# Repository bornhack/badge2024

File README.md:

# BornHack badge 2024

## Firmware

[Initial firmware](https://github.com/badgeteam/bornhack2024-firmware) ([Flasher tool](https://github.com/badgeteam/bornhack2024-flasher))

[Pwnies ESP32-C3 Firmware Examples](https://github.com/Pwnies/bornhack-badge-esp32-c3-rust)

[Orange Murker workshop POV firmware](https://github.com/Orange-Murker/bh25-rs)

[3D Printed Case](https://github.com/bornhack/badge2024/tree/case)

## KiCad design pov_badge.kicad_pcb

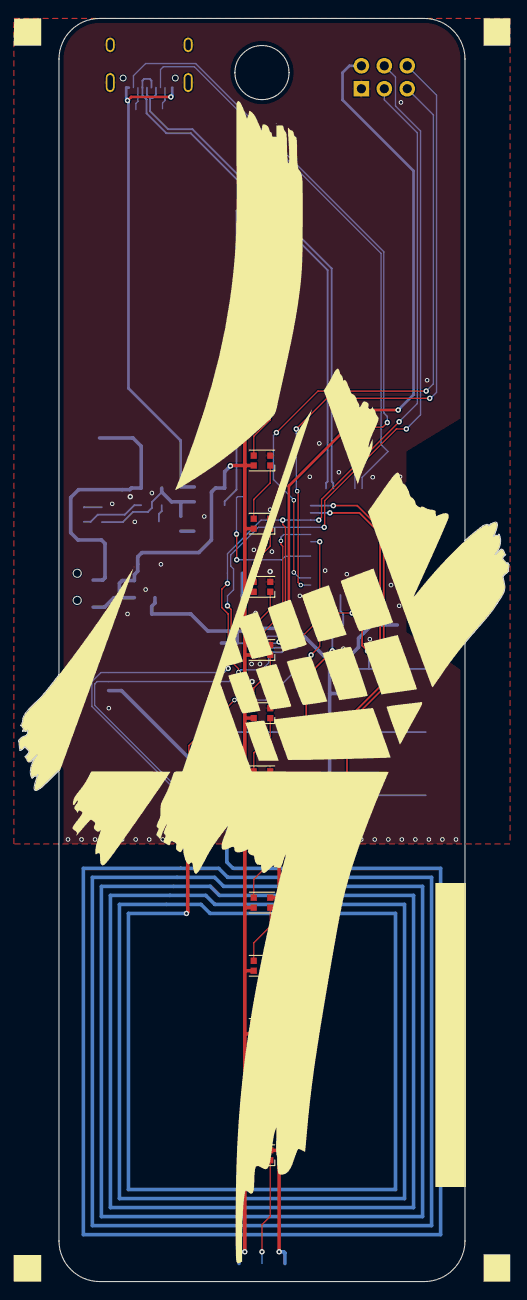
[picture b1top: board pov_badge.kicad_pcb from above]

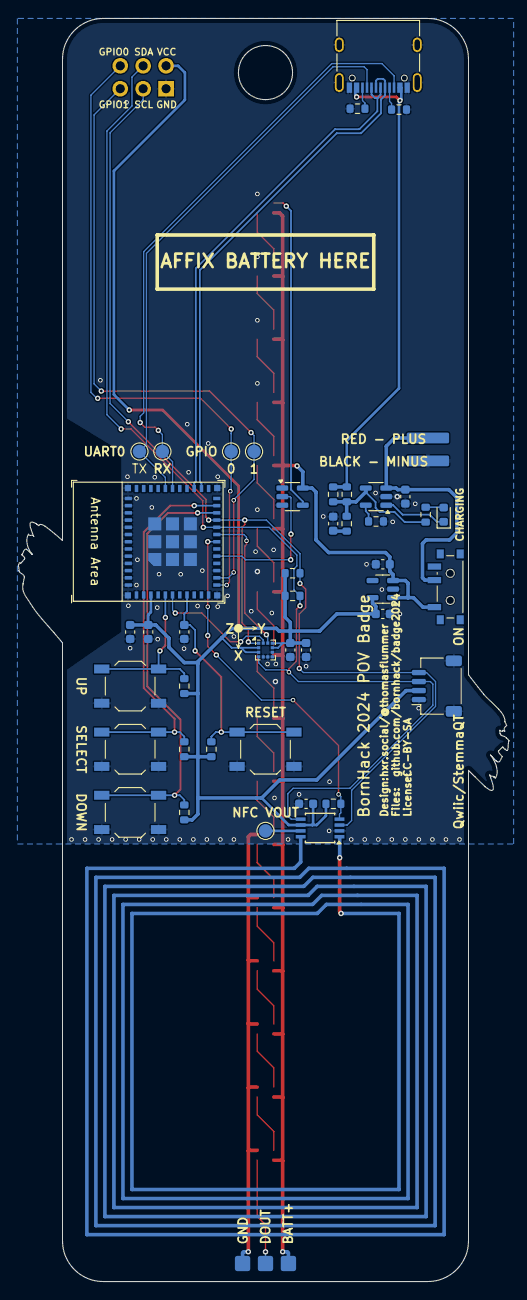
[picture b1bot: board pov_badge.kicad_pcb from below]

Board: 2 copper layers, 54.4 x 140.0 mm, 62 parts (45 on the bottom side), 47 nets.

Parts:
C1, C8, C10: 100nF; C_0603_1608Metric
C2: 4.7uF; C_0603_1608Metric
C3, C4, C7: 1uF; C_0603_1608Metric
C5: 100nf; C_0603_1608Metric
C6, C9: 10uF; C_0603_1608Metric
D1, D2, D3, D4, D5, D6, D7, D8, D9, D10, D11, D12, D13, D14, D15, D16: WS2812B-2020; LED_WS2812B-2020_PLCC4_2.0x2.0mm
D17: CHRG; LED_0603_1608Metric
J1: LED_OUT; PinHeader_1x03_P2.54mm_Horizontal
J2: LiPo 1S; PinHeader_1x02_P2.54mm_Vertical
J3: USB_C_Receptacle_USB2.0_16P; USB_C_Receptacle_XKB_U262-16XN-4BVC11
J4: Qwiic; JST_SH_SM04B-SRSS-TB_1x04-1MP_P1.00mm_Horizontal
R1, R11, R12, R13, R14: 10K; R_0603_1608Metric
R2, R4, R5: 1; R_0603_1608Metric
R3: 1k; R_0603_1608Metric
R6: 2k; R_0603_1608Metric
R7, R8: 10k; R_0603_1608Metric
R9, R10: 5.1K; R_0603_1608Metric
SW1: UP; SW_SPST_TL3342
SW2: DOWN; SW_SPST_TL3342
SW3: POWER; SW_SPDT_PCM12
SW4: RESET; SW_SPST_TL3342
SW5: SELECT; SW_SPST_TL3342
TP1: NFC_VOUT; TestPoint_Pad_D1.5mm
TP2: GPIO1; TestPoint_Pad_D1.5mm
TP3: GPIO0; TestPoint_Pad_D1.5mm
TP4: TX0; TestPoint_Pad_D1.5mm
TP5: RX0; TestPoint_Pad_D1.5mm
U1: HX4054A; SOT-23-5
U2: AP2112K-3.3; SOT-23-5
U3: NT3H2x11; TSSOP-8_3x3mm_P0.65mm
U4: ESP32-C3-MINI-1
U5: 74LVC1G17; SOT-23-5
U6: LIS2Dx12; LGA-12_2x2mm_P0.5mm
X1: #badgelife; Badgelife-SAOv169-BADGE-2x3

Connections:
+BATT: C3.1, D1.4 (VDD), D2.4 (VDD), D3.4 (VDD), D4.4 (VDD), D5.4 (VDD), D6.4 (VDD), D7.4 (VDD), D8.4 (VDD), D9.4 (VDD), D10.4 (VDD), D11.4 (VDD), D12.4 (VDD), D13.4 (VDD), D14.4 (VDD), D15.4 (VDD), D16.4 (VDD), J1.1, SW3.1 (A), U2.1 (VIN), U2.3 (EN), U5.5 (VCC)
/1S Lipo/BATT_PLUS: C2.1, J2.1, SW3.2 (B), U1.3 (BAT)
/1S Lipo/CHG_INDICATION: D17.1 (K), U1.1 (~CHRG)
/1S Lipo/VUSB: J3.A4 (VBUS), J3.A9 (VBUS), J3.B4 (VBUS), J3.B9 (VBUS), R4.2, R5.2
/16 x WS2812/DOUT: D16.1 (DOUT), J1.2
/ACC_INT1: U4.6 (GPIO3/ADC1_CH3), U6.12 (INT1)
/ACC_INT2: U4.19 (GPIO5/ADC2_CH0), U6.11 (INT2)
/ESP32-C3 mini module/GPIO9_BOOT_SEL: R14.2, SW5.1, U4.23 (GPIO9)
/ESP32-C3 mini module/N_RST: C7.1, R11.2, SW4.2, U4.8 (EN/CHIP_PU)
/ESP32-C3 mini module/RX0: J3.B8 (SBU2), TP5.1, U4.30 (GPIO20/U0RXD)
/ESP32-C3 mini module/TX0: J3.A8 (SBU1), TP4.1, U4.31 (GPIO21/U0TXD)
/ESP32-C3 mini module/USB_D+: J3.A6 (D+), J3.B6 (D+), U4.27 (GPIO19/USB_D+)
/ESP32-C3 mini module/USB_D-: J3.A7 (D-), J3.B7 (D-), U4.26 (GPIO18/USB_D-)
/FD: R1.2, U3.4 (FD), U4.18 (GPIO4/ADC1_CH4)
/GPIO0: TP3.1, U4.12 (GPIO0/ADC1_CH0/XTAL_32K_P), X1.5 (GPIO1)
/GPIO1: TP2.1, U4.13 (GPIO1/ADC1_CH1/XTAL_32K_N), X1.6 (GPIO2)
/LED_DATA: U4.16 (GPIO10), U5.2
/NFC NTAG/COIL: U3.1 (LA), U3.8 (LB)
/NFC NTAG/VOUT: TP1.1, U3.7 (Vout)
/SCL: J4.4, R7.2, U3.3 (SCL), U4.21 (GPIO7), U6.1 (SCL/SPC), X1.4 (SCL)
/SDA: J4.3, R8.2, U3.5 (SDA), U4.20 (GPIO6), U6.4 (SDA/SDI/SDO), X1.3 (SDA)
/SW_DOWN: R13.2, SW2.1, U4.22 (GPIO8)
/SW_UP: R12.2, SW1.1, U4.5 (GPIO2/ADC1_CH2)
GND: C1.2, C2.2, C3.2, C4.2, C5.2, C6.2, C7.2, C8.2, C9.2, C10.2, D1.2 (VSS), D2.2 (VSS), D3.2 (VSS), D4.2 (VSS), D5.2 (VSS), D6.2 (VSS), D7.2 (VSS), D8.2 (VSS), D9.2 (VSS), D10.2 (VSS), D11.2 (VSS), D12.2 (VSS), D13.2 (VSS), D14.2 (VSS), D15.2 (VSS), D16.2 (VSS), J1.3, J2.2, J3.A1 (GND), J3.A12 (GND), J3.B1 (GND), J3.B12 (GND), J3.S1 (SHIELD), J4.1, J4.MP, R6.1, R9.2, R10.2, SW1.2, SW2.2, SW4.1, SW5.2, U1.2 (GND), U2.2 (GND), U3.2 (VSS), U4.1 (GND), U4.2 (GND), U4.11 (GND), U4.14 (GND), U4.36 (GND), U4.37 (GND), U4.38 (GND), U4.39 (GND), U4.40 (GND), U4.41 (GND), U4.42 (GND), U4.43 (GND), U4.44 (GND), U4.45 (GND), U4.46 (GND), U4.47 (GND), U4.48 (GND), U4.49 (GND), U4.50 (GND), U4.51 (GND), U4.52 (GND), U4.53 (GND), U5.3 (GND), U6.5 (RES(GND)), U6.6 (GND), U6.7 (GND), U6.8 (GND), X1.2 (GND)
unnamed: C1.1, R2.1
unnamed: D1.3 (DIN), U5.4
unnamed: D1.1 (DOUT), D2.3 (DIN)
unnamed: D2.1 (DOUT), D3.3 (DIN)
unnamed: D3.1 (DOUT), D4.3 (DIN)
unnamed: D4.1 (DOUT), D5.3 (DIN)
unnamed: D5.1 (DOUT), D6.3 (DIN)
unnamed: D6.1 (DOUT), D7.3 (DIN)
unnamed: D7.1 (DOUT), D8.3 (DIN)
unnamed: D8.1 (DOUT), D9.3 (DIN)
unnamed: D9.1 (DOUT), D10.3 (DIN)
unnamed: D10.1 (DOUT), D11.3 (DIN)
unnamed: D11.1 (DOUT), D12.3 (DIN)
unnamed: D12.1 (DOUT), D13.3 (DIN)
unnamed: D13.1 (DOUT), D14.3 (DIN)
unnamed: D14.1 (DOUT), D15.3 (DIN)
unnamed: D15.1 (DOUT), D16.3 (DIN)
unnamed: D17.2 (A), R3.1
unnamed: J3.A5 (CC1), R9.1
unnamed: J3.B5 (CC2), R10.1
unnamed: R6.2, U1.5 (PROG)
unnamed: R2.2, R3.2, R4.1, R5.1, U1.4 (VCC)
VCC: C4.1, C5.1, C6.1, C8.1, C9.1, C10.1, J4.2, R1.1, R7.1, R8.1, R11.1, R12.1, R13.1, R14.1, U2.5 (VOUT), U3.6 (VCC), U4.3 (3V3), U6.2 (CS), U6.3 (SDO/SA0), U6.9 (VDD), U6.10 (VDD-IO), X1.1 (VCC)

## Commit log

2025-07-20 Integrate a bit
2025-07-20 move stuff
2025-07-20 workspace features
2025-07-20 Fix the ws2812b code
2025-07-20 Closer to compiling
2025-07-20 It compiles?
2025-07-20 Closer to working
2025-07-20 Stuff works
2025-07-20 fixes
2025-07-20 Fix message types
2025-07-20 Fix run.sh
2025-07-20 zsh wtf
2025-07-20 More tasks so we can connect 2 at once
2025-07-21 Bump rust edition, small cleanup
2025-07-21 clippy
2025-07-21 Make all examples work with new espflash version
2025-07-21 Standardize wifi env vars
2025-07-22 Minimal README
2025-07-22 Links added
2025-07-23 Add FreeCAD project
2025-07-23 Add STL files
2025-07-23 Add README.md
2025-07-23 Add demo photos
2025-07-23 Add pictures to readme
2025-08-06 Add link to case branch

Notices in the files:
pov_badge.kicad_pcb:
License:
CC-BY-SA
